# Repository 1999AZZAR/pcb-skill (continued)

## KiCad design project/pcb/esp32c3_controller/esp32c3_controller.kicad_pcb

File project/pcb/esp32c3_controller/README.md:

# ESP32-C3 Motion Controller & Gamepad

Compact 2-layer handheld motion controller and gamepad designed in KiCad 9 for JLCPCB manufacturing and SMT assembly.

---

## 1. Hardware Architecture

* **MCU**: Espressif ESP32-C3-WROOM-02-N4 (32-bit RISC-V @ 160 MHz, 4MB Flash, 2.4 GHz Wi-Fi 4 & Bluetooth 5 LE).
* **Display**: 0.96" 128×64 I2C OLED (SSD1306) on 1×04 2.54mm pin header.
* **IMU**: InvenSense MPU-6050 6-axis Gyroscope + Accelerometer (QFN-24) with hardware motion processing and interrupt output.
* **Navigation Inputs**: 5 tactile pushbuttons (`UP`, `DOWN`, `LEFT`, `RIGHT`, `SELECT`) with 10kΩ external pull-ups and 100nF debounce capacitors.
* **System Inputs**: Dedicated hardware `RESET` and `BOOT` tactile buttons.
* **Power Management**:
  * USB Type-C 16-pin connector with dual 5.1kΩ CC pull-down resistors (standard UFP / 5V 3A sinking).
  * AMS1117-3.3 SOT-223 Low-Dropout Regulator (800mA max output) with 10µF input/output decoupling.
  * Status indicator LED on +3.3V rail and programmable GPIO status LED.
* **Connectivity**: Native USB D+/D- directly routed with differential impedance matching to ESP32-C3 GPIO18/GPIO19 (USB CDC / JTAG).

---

## 2. Pinout Mapping

| Component | Signal | ESP32-C3 GPIO | Description |
| :--- | :--- | :--- | :--- |
| **I2C Bus** | `I2C_SDA` | GPIO4 | Shared SDA for SSD1306 & MPU-6050 (4.7kΩ pull-up) |
| | `I2C_SCL` | GPIO5 | Shared SCL for SSD1306 & MPU-6050 (4.7kΩ pull-up) |
| **MPU-6050** | `MPU_INT` | GPIO6 | Motion interrupt trigger |
| **Buttons** | `BTN_UP` | GPIO0 | Directional Up button (active low) |
| | `BTN_DOWN` | GPIO1 | Directional Down button (active low) |
| | `BTN_LEFT` | GPIO2 | Directional Left button (active low) |
| | `BTN_RIGHT` | GPIO3 | Directional Right button (active low) |
| | `BTN_SELECT` | GPIO7 | Action/Select button (active low) |
| **System** | `ESP_EN` | `CHIP_EN` | Hardware Reset with 10kΩ pull-up & 1µF RC delay |
| | `ESP_BOOT` | GPIO9 | Bootloader mode button (active low) |
| **Status** | `STATUS_LED` | GPIO10 | User programmable indicator LED |
| **USB Native**| `USB_D_N` | GPIO18 | USB Full-Speed D- |
| | `USB_D_P` | GPIO19 | USB Full-Speed D+ |

---

## 3. PCB & Manufacturing Specifications

* **Dimensions**: 85.0 mm × 55.0 mm (Credit card footprint).
* **Layer Count**: 2 Layers (Top: `F.Cu`, Bottom: `B.Cu`).
* **Substrate**: FR4, 1.6 mm thickness.
* **Copper Weight**: 1 oz (35 µm).
* **Surface Finish**: HASL with lead / ENIG compatible.
* **Trace Clearance**: Min 0.15 mm clearance, min 0.20 mm track width (0.35 mm for power nets).
* **Vias**: 0.60 mm diameter, 0.30 mm drill (JLCPCB standard capability).
* **Planes**: Solid GND copper flood on both `F.Cu` and `B.Cu` with stitching vias and RF keepout under the onboard PCB antenna.
* **DRC Verification**: **0 Errors, 0 Warnings, 0 Unconnected Items** via `kicad-cli pcb drc`.

---

## 4. Production Files (`jlcpcb_production/`)

Ready for 1-click ordering on JLCPCB:

* **Gerbers & Drill ZIP**: `esp32c3_controller_gerber_jlcpcb.zip`
* **Bill of Materials**: `esp32c3_controller_bom_jlcpcb.csv` (includes matched LCSC part numbers)
* **Centroid / Pick-and-Place**: `esp32c3_controller_cpl_jlcpcb.csv` (JLCPCB standard SMT column headers)
* **3D Photorealistic Previews**: `esp32c3_controller_render_top.png` and `esp32c3_controller_render_bottom.png`

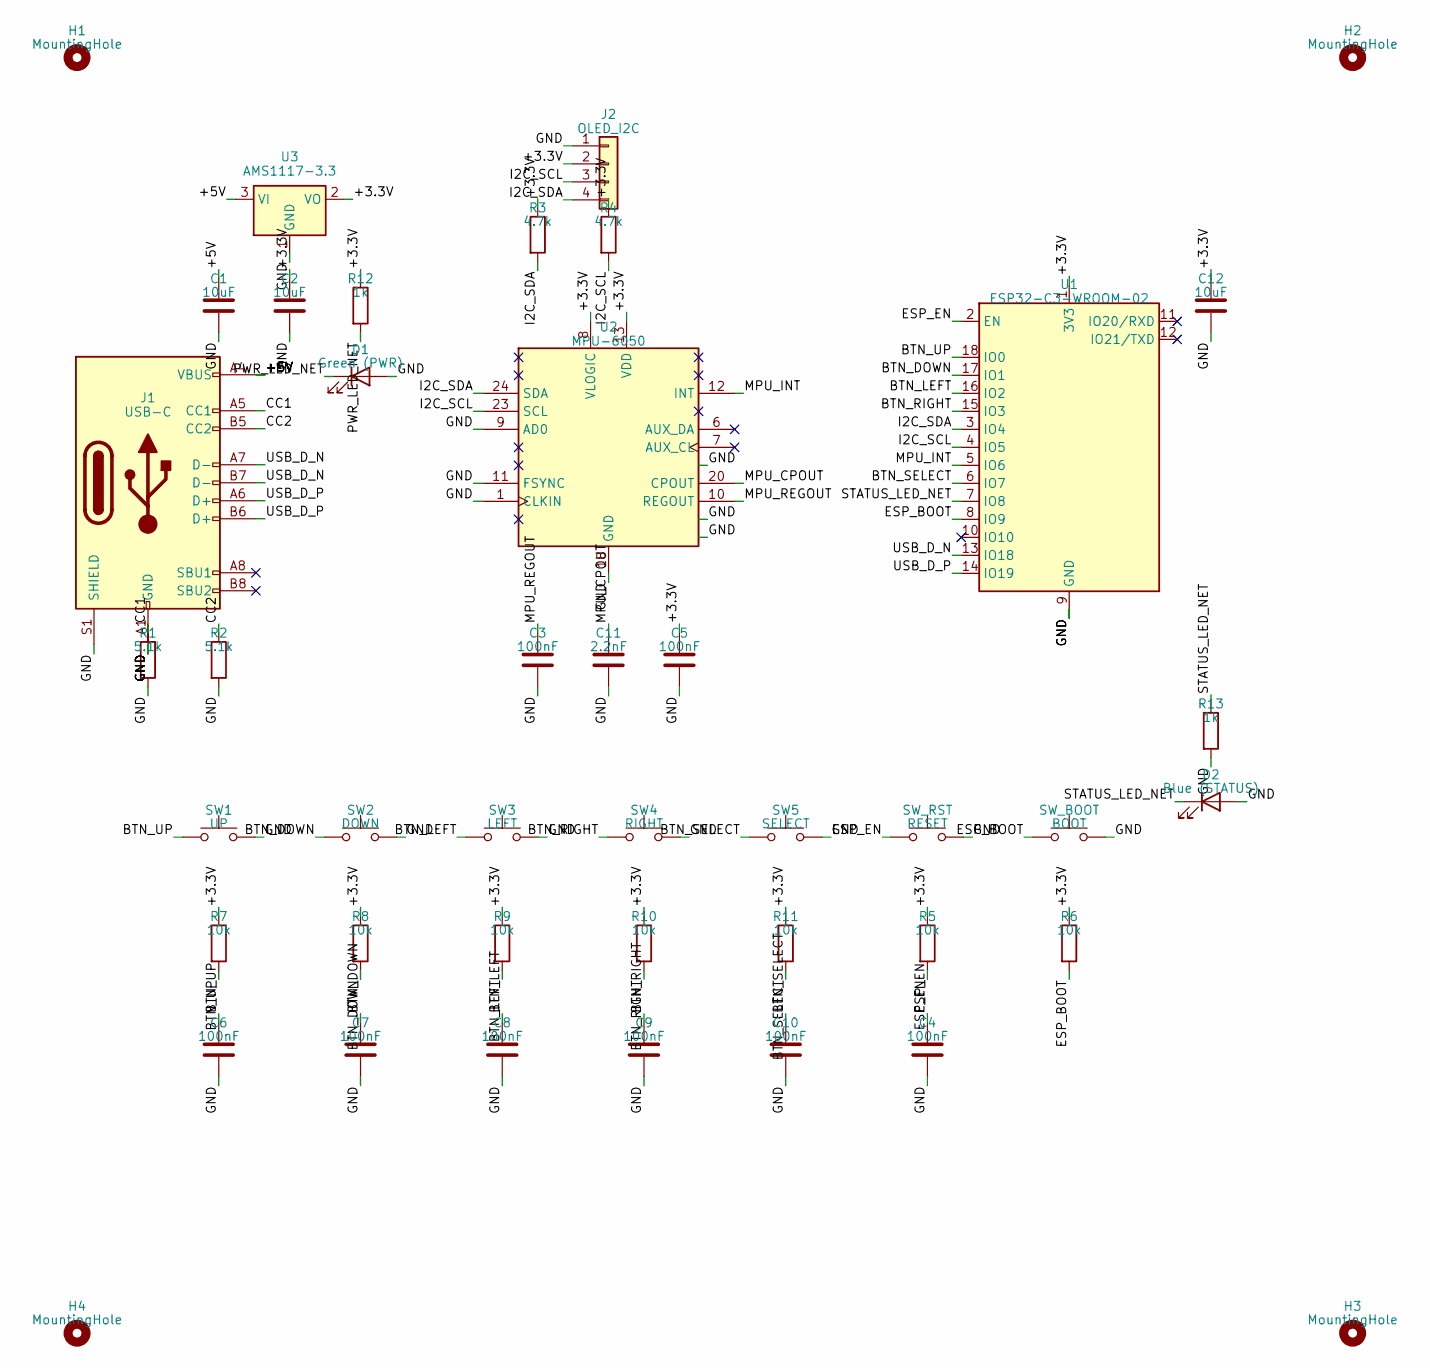
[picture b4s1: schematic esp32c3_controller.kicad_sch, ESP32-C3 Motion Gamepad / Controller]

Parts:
C1, C2, C12: 10uF; C_0805_2012Metric
C3, C4, C5, C6, C7, C8, C9, C10: 100nF; C_0805_2012Metric
C11: 2.2nF; C_0805_2012Metric
D1: Green (PWR); LED_0805_2012Metric
D2: Blue (STATUS); LED_0805_2012Metric
H1, H2, H3, H4: MountingHole; MountingHole_3.2mm_M3
J1: USB-C; USB_C_Receptacle_HRO_TYPE-C-31-M-12
J2: OLED_I2C; PinHeader_1x04_P2.54mm_Vertical
R1, R2: 5.1k; R_0805_2012Metric
R3, R4: 4.7k; R_0805_2012Metric
R5, R6, R7, R8, R9, R10, R11: 10k; R_0805_2012Metric
R12, R13: 1k; R_0805_2012Metric
SW1: UP; SW_Push_1P1T_XKB_TS-1187A
SW2: DOWN; SW_Push_1P1T_XKB_TS-1187A
SW3: LEFT; SW_Push_1P1T_XKB_TS-1187A
SW4: RIGHT; SW_Push_1P1T_XKB_TS-1187A
SW5: SELECT; SW_Push_1P1T_XKB_TS-1187A
SW_BOOT: BOOT; SW_Push_1P1T_XKB_TS-1187A
SW_RST: RESET; SW_Push_1P1T_XKB_TS-1187A
U1: ESP32-C3-WROOM-02
U2: MPU-6050; InvenSense_QFN-24_4x4mm_P0.5mm
U3: AMS1117-3.3; SOT-223-3_TabPin2

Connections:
+3.3V: C2.1, C5.1, C12.1, J2.2, R3.1, R4.1, R5.1, R6.1, R7.1, R8.1, R9.1, R10.1, R11.1, R12.1, U1.1 (3V3), U2.8 (VLOGIC), U2.13 (VDD), U3.2 (VO)
+5V: C1.1, J1.A4 (VBUS), J1.A9 (VBUS), J1.B4 (VBUS), J1.B9 (VBUS), U3.3 (VI)
BTN_DOWN: C7.1, R8.2, SW2.1, U1.17 (IO1)
BTN_LEFT: C8.1, R9.2, SW3.1, U1.16 (IO2)
BTN_RIGHT: C9.1, R10.2, SW4.1, U1.15 (IO3)
BTN_SELECT: C10.1, R11.2, SW5.1, U1.6 (IO7)
BTN_UP: C6.1, R7.2, SW1.1, U1.18 (IO0)
CC1: J1.A5 (CC1), R1.1
CC2: J1.B5 (CC2), R2.1
ESP_BOOT: R6.2, SW_BOOT.1, U1.8 (IO9)
ESP_EN: C4.1, R5.2, SW_RST.1, U1.2 (EN)
GND: C1.2, C2.2, C3.2, C4.2, C5.2, C6.2, C7.2, C8.2, C9.2, C10.2, C11.2, C12.2, D1.2 (A), D2.2 (A), J1.A1 (GND), J1.A12 (GND), J1.B1 (GND), J1.B12 (GND), J1.S1 (SHIELD), J2.1, R1.2, R2.2, R13.2, SW1.2, SW2.2, SW3.2, SW4.2, SW5.2, SW_BOOT.2, SW_RST.2, U1.9 (GND), U1.19 (GND), U2.1 (CLKIN), U2.9 (AD0), U2.11 (FSYNC), U2.18 (GND), U2.19 (RESV), U2.21 (RESV), U2.22 (RESV), U3.1 (GND)
I2C_SCL: J2.3, R4.2, U1.4 (IO5), U2.23 (SCL)
I2C_SDA: J2.4, R3.2, U1.3 (IO4), U2.24 (SDA)
MPU_CPOUT: C11.1, U2.20 (CPOUT)
MPU_INT: U1.5 (IO6), U2.12 (INT)
MPU_REGOUT: C3.1, U2.10 (REGOUT)
PWR_LED_NET: D1.1 (K), R12.2
STATUS_LED_NET: D2.1 (K), R13.1, U1.7 (IO8)
USB_D_N: J1.A7 (D-), J1.B7 (D-), U1.13 (IO18)
USB_D_P: J1.A6 (D+), J1.B6 (D+), U1.14 (IO19)

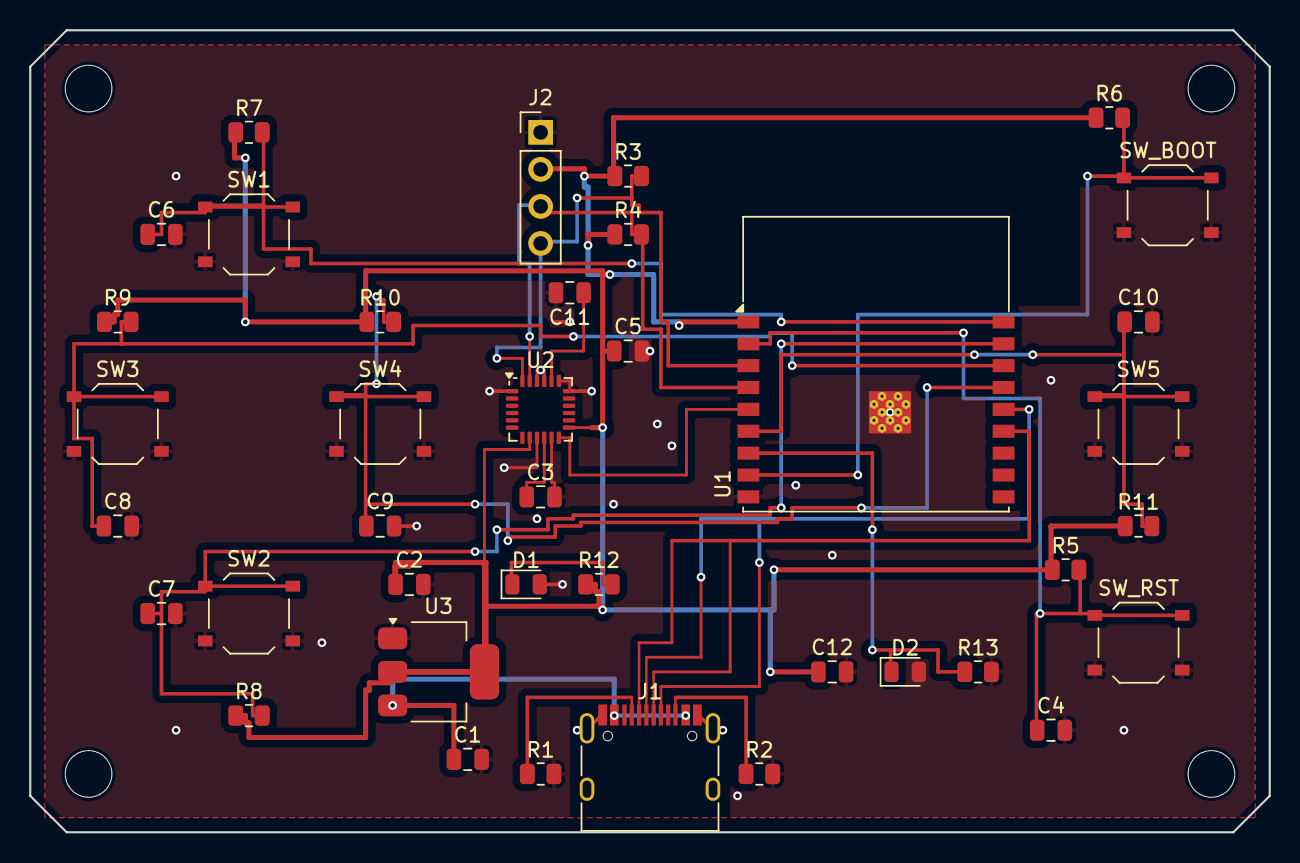
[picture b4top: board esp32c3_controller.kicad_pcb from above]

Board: 2 copper layers, 85.0 x 55.0 mm, 43 parts (0 on the bottom side), 21 nets.

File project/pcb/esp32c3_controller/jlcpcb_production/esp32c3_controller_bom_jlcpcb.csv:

"Refs","Value","Footprint","Qty","DNP"
"C1","10uF","Capacitor_SMD:C_0805_2012Metric","1",""
"C2","10uF","Capacitor_SMD:C_0805_2012Metric","1",""
"C3","100nF","Capacitor_SMD:C_0805_2012Metric","1",""
"C4","100nF","Capacitor_SMD:C_0805_2012Metric","1",""
"C5","100nF","Capacitor_SMD:C_0805_2012Metric","1",""
"C6","100nF","Capacitor_SMD:C_0805_2012Metric","1",""
"C7","100nF","Capacitor_SMD:C_0805_2012Metric","1",""
"C8","100nF","Capacitor_SMD:C_0805_2012Metric","1",""
"C9","100nF","Capacitor_SMD:C_0805_2012Metric","1",""
"C10","100nF","Capacitor_SMD:C_0805_2012Metric","1",""
"C11","2.2nF","Capacitor_SMD:C_0805_2012Metric","1",""
"C12","10uF","Capacitor_SMD:C_0805_2012Metric","1",""
"D1","Green (PWR)","LED_SMD:LED_0805_2012Metric","1",""
"D2","Blue (STATUS)","LED_SMD:LED_0805_2012Metric","1",""
"J1","USB-C","Connector_USB:USB_C_Receptacle_HRO_TYPE-C-31-M-12","1",""
"J2","OLED_I2C","Connector_PinHeader_2.54mm:PinHeader_1x04_P2.54mm_Vertical","1",""
"R1","5.1k","Resistor_SMD:R_0805_2012Metric","1",""
"R2","5.1k","Resistor_SMD:R_0805_2012Metric","1",""
"R3","4.7k","Resistor_SMD:R_0805_2012Metric","1",""
"R4","4.7k","Resistor_SMD:R_0805_2012Metric","1",""
"R5","10k","Resistor_SMD:R_0805_2012Metric","1",""
"R6","10k","Resistor_SMD:R_0805_2012Metric","1",""
"R7","10k","Resistor_SMD:R_0805_2012Metric","1",""
"R8","10k","Resistor_SMD:R_0805_2012Metric","1",""
"R9","10k","Resistor_SMD:R_0805_2012Metric","1",""
"R10","10k","Resistor_SMD:R_0805_2012Metric","1",""
"R11","10k","Resistor_SMD:R_0805_2012Metric","1",""
"R12","1k","Resistor_SMD:R_0805_2012Metric","1",""
"R13","1k","Resistor_SMD:R_0805_2012Metric","1",""
"SW1","UP","Button_Switch_SMD:SW_Push_1P1T_XKB_TS-1187A","1",""
"SW2","DOWN","Button_Switch_SMD:SW_Push_1P1T_XKB_TS-1187A","1",""
"SW3","LEFT","Button_Switch_SMD:SW_Push_1P1T_XKB_TS-1187A","1",""
"SW4","RIGHT","Button_Switch_SMD:SW_Push_1P1T_XKB_TS-1187A","1",""
"SW5","SELECT","Button_Switch_SMD:SW_Push_1P1T_XKB_TS-1187A","1",""
"SW_BOOT?","BOOT","Button_Switch_SMD:SW_Push_1P1T_XKB_TS-1187A","1",""
"SW_RST?","RESET","Button_Switch_SMD:SW_Push_1P1T_XKB_TS-1187A","1",""
"U1","ESP32-C3-WROOM-02","RF_Module:ESP32-C3-WROOM-02","1",""
"U2","MPU-6050","Sensor_Motion:InvenSense_QFN-24_4x4mm_P0.5mm","1",""
"U3","AMS1117-3.3","Package_TO_SOT_SMD:SOT-223-3_TabPin2","1",""
